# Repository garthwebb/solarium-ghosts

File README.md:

# solarium-ghosts
A project to repurpose the lights from the Solarium as standalone strings of 16 lights

Note: This includes a copy of the i2c code at https://github.com/g4lvanix/I2C-master-lib

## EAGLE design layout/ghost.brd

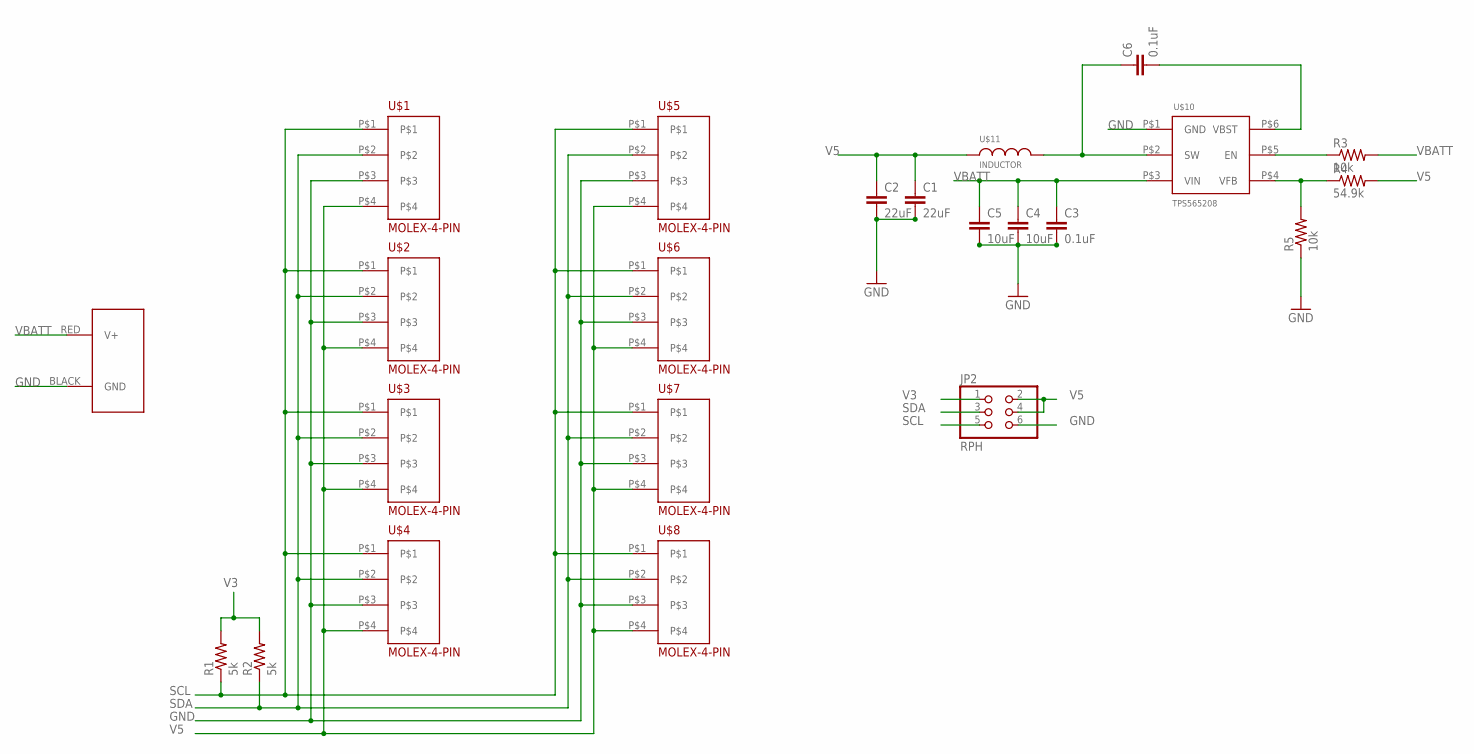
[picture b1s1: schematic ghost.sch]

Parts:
C1, C2: 22uF; 0805
C3, C6: 0.1uF; 0805
C4, C5: 10uF; 0805
J1: POWERPOLE_POWER45A_HORIZONTAL_DRILL; POWERPOLE_PAIR_45A_HORIZ_HOLE
JP2: RPH; 2X03
R1, R2: 5k; 0805
R3, R5: 10k; 0805
R4: 54.9k; 0805
U$1, U$2, U$3, U$4, U$5, U$6, U$7, U$8: MOLEX-4-PIN
U$10: TPS565208; SOT-23-THIN-6
U$11: INDUCTOR; 0805

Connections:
GND: C1.2, C2.2, C3.2, C4.2, C5.2, J1.BLACK (GND), JP2.6, R5.1, U$1.P$3, U$2.P$3, U$3.P$3, U$4.P$3, U$5.P$3, U$6.P$3, U$7.P$3, U$8.P$3, U$10.P$1 (GND)
unnamed: C6.1, U$10.P$2 (SW), U$11.P$2 (2)
unnamed: R3.1, U$10.P$5 (EN)
unnamed: C6.2, U$10.P$6 (VBST)
unnamed: R4.1, R5.2, U$10.P$4 (VFB)
SCL: JP2.5, R1.1, U$1.P$1, U$2.P$1, U$3.P$1, U$4.P$1, U$5.P$1, U$6.P$1, U$7.P$1, U$8.P$1
SDA: JP2.3, R2.1, U$1.P$2, U$2.P$2, U$3.P$2, U$4.P$2, U$5.P$2, U$6.P$2, U$7.P$2, U$8.P$2
V3: JP2.1, R1.2, R2.2
V5: C1.1, C2.1, JP2.2, JP2.4, R4.2, U$1.P$4, U$2.P$4, U$3.P$4, U$4.P$4, U$5.P$4, U$6.P$4, U$7.P$4, U$8.P$4, U$11.P$1 (1)
VBATT: C3.1, C4.1, C5.1, J1.RED (V+), R3.2, U$10.P$3 (VIN)

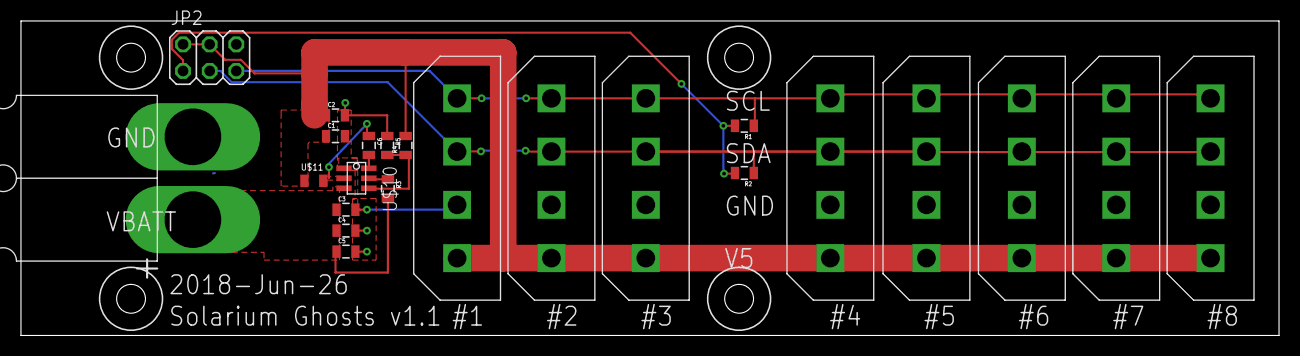
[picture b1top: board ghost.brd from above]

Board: 2 copper layers, 120.0 x 30.0 mm, 23 parts (0 on the bottom side), 10 nets.

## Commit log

2018-03-07 First checkin
2018-03-07 Added submodule for I2C stuff
2018-03-07 Eh, nevermind, just copy the files locally since they need to be edited for this project
2018-03-07 Cleanup
2018-03-09 Oooookay, it doesn't seem like C++ is a slam dunk for AVR code.
    Checkpointing here before converting it all back to C
2018-03-09 Missed in last checkpoint before converting back to C
2018-03-10 Get rid of C++ code
2018-03-10 Makefile plus serial lib plus updated C version of CPP lib
2018-03-10 Whoops, this checkin actually has all the C++ -> C changes
2018-03-10 Figured out/remembered the LSB needed to be 1 or 0
    0 is for write requests
    1 is for read requests
    The top MSB are for the actual address of the device
2018-03-10 Auto detect rays implemented
    * Probe i2c bus added
    * device list struct
    * ray list struct
2018-03-13 Update i2c bus speed to 400kHz
2018-03-13 Added HSV conversion code
2018-03-13 Added some debugging
2018-03-13 Try to work with the HSV code.
    Running into memory issues with malloc. Reaching the 16k limit on the atmega168.
2018-03-13 Move a few common libs into one place
2018-03-13 Update the makefile
2018-03-13 Move everything into a project folder
2018-03-15 Checkpoint basic version of code without as much abtraction
    Still running out of memory. Next trying version that does not use malloc
2018-07-03 Checkin several C tests, plus all the layout docs
2018-07-03 First OSHPark file from 2018-06-03
2018-07-03 New verion of file from 2018-06-26.
    Fixed problems in first board
2018-07-03 Updated silk screen, reordered some text. From 2018-06-27
2018-07-03 First verion of seeed studio layout file. Uses RS-274 output
    From 2018-06-04
2018-07-03 New version of layout that fixes bugs in first board.
    A rerun of the OSHPark version with RS-274 output
    From 2018-06-27
2018-07-04 New files for accessing the PCA9635 LED controller, the ray its on and the i2c bus
2018-07-04 Update to ignore compiled py, export the i2c class
2018-07-04 New controller, plus drivers, generators and a script to start the show
2018-07-04 Abstract bus out to the i2c object
2018-07-04 Moved ray and i2c to the driver folder
2018-07-04 Add the bluetooth driver
2018-07-04 Add test generator
2018-07-04 Initialize the generators array to an empty array
2018-07-04 Fix argument passing for init and make range work correctly for initializing rays
2018-07-04 Add some debugging
2018-07-04 Iterate over addresses properly
2018-07-04 Make sure MAX_LED_VALUE is defined
2018-07-04 Add placeholder args for later use
2018-07-04 Set generator if its passed on the command line
2018-07-04 Fix some errors
2018-07-04 Initialize the led values array correctly
2018-07-04 Let the generators make a full set of ray data but don't try to write it if not all rays are plugged in
2018-07-04 Allow fps to be set on the command line
2018-07-04 Convert string arg to int
2018-07-04 Initialize without pointers to the same list
